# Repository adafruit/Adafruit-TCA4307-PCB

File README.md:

## Adafruit TCA4307 Hot-Swap I2C Buffer with Stuck Bus Recovery PCB

<a href="http://www.adafruit.com/products/5159"><br/>
Click here to purchase one from the Adafruit shop</a>

PCB files for the Adafruit TCA4307 Hot-Swap I2C Buffer with Stuck Bus Recovery. 

Format is EagleCAD schematic and board layout
* https://www.adafruit.com/product/5159

### Description

As we've been adding  STEMMA QT connectors to our breakouts and dev boards, folks have been really enjoying the simplicity and speed of plugging in I2C sensors and devices for quick iteration and design. That's all good, but I2C wasn't really designed for hot-plugging. You're kinda supposed to have everything connected once on boot and never mess with it - I2C was specified for on-board connections. And, folks who have experimented with hot-plugging I2C devices eventually have discovered that if you plug in or unplug at the wrong moment you can cause the bus to hang due to an extra SCL pulse or an unexpected capacitive load.

The Adafruit TCA4307 Hot-Swap I2C Buffer breakout here solves that problem. It's specifically designed to take a non-hot-swap protocol (I2C) and protect the controller from wayward peripherals messing with the bus during attach/detach.

Usage is super simple. Connect the left side (IN) to your main board controller - Arduino, Raspberry Pi, Feather, etc. Then connect any I2C sensors you like to OUT side. Power is connected through - this isn't a power isolator, just a bus buffer. You can use 2.3 to 5.5V DC power and logic levels.

The chip can handle up to 400KHz I2C clock rates and even has stuck bus recovery: it automatically disconnects the bus if it detects either SDAOUT or SCLOUT are low for about 40 ms. Once the bus is disconnected, the device automatically generates up to 16 pulses on SCLOUT to attempt to reset the device which is holding the bus low.

There's also an extra ENable pin, if you want to disconnect the in and out sides, and a READY pin that will let you know if the peripheral is buffer-connected to the controller (and is safe to attempt communication with)

To get you going fast, we spun up a custom-made PCB in the STEMMA QT form factor, making it easy to interface with. The STEMMA QT connectors on either side are compatible with the SparkFun Qwiic I2C connectors. This allows you to make solderless connections between your development board and the TCA4307 or to chain it with a wide range of other sensors and accessories using a compatible cable. QT Cable is not included, but we have a variety in the shop.

### License

Adafruit invests time and resources providing this open source design, please support Adafruit and open-source hardware by purchasing products from [Adafruit](https://www.adafruit.com)!

Designed by Limor Fried/Ladyada for Adafruit Industries.

Creative Commons Attribution/Share-Alike, all text above must be included in any redistribution. 
See license.txt for additional details.

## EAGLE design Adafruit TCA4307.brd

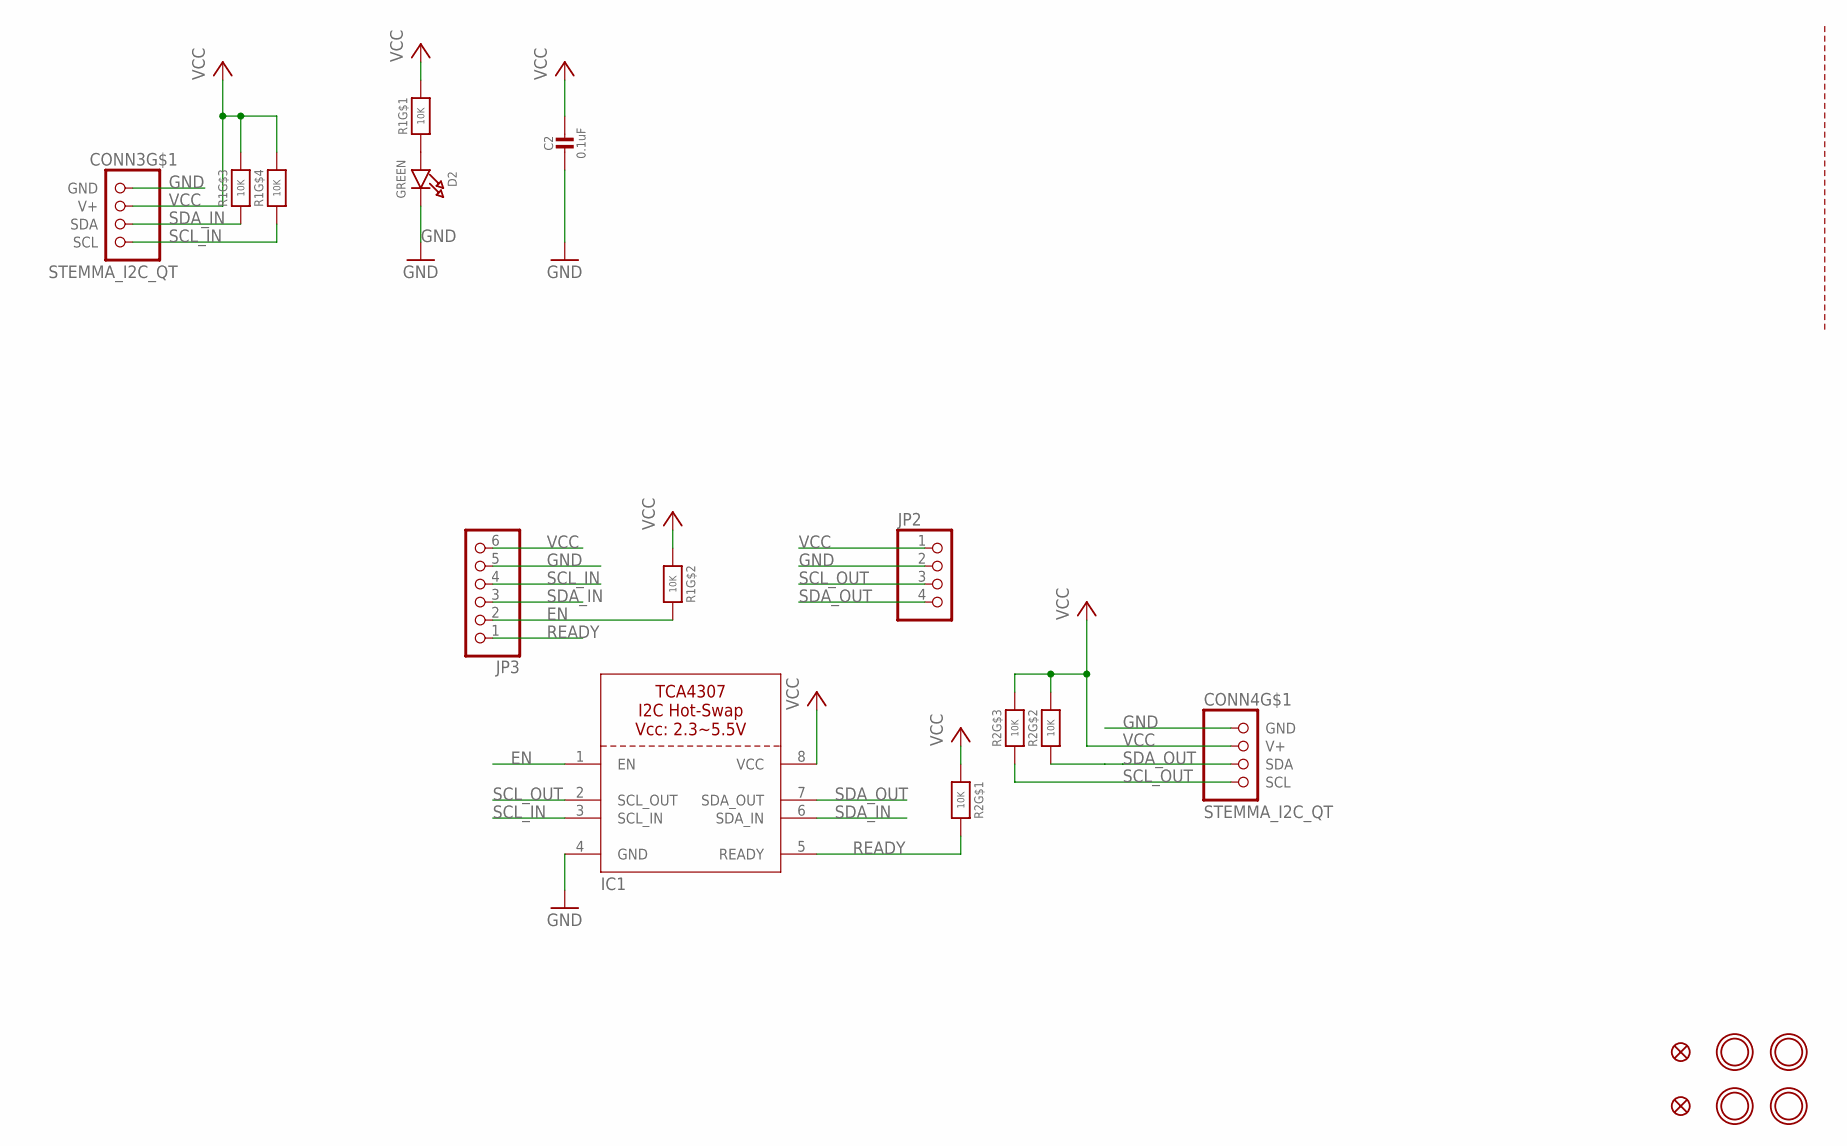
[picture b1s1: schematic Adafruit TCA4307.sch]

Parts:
C2: 0.1uF; 0603-NO
CONN3, CONN4: STEMMA_I2C_QT; JST_SH4
D2: GREEN; CHIPLED_0603_NOOUTLINE
FID3, FID4: FIDUCIAL_1MM
IC1: TCA4307; TSSOP8
JP2: HEADER-1X4ROUND; 1X04_ROUND
JP3: HEADER-1X670MIL; 1X06_ROUND_70
R1, R2: 10K; RESPACK_4X0603
U$1, U$17, U$19, U$21: MOUNTINGHOLE2.5; MOUNTINGHOLE_2.5_PLATED

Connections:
EN: IC1.1 (EN), JP3.2, R1.7 (2)
GND: C2.2, CONN3.1 (GND), CONN4.1 (GND), D2.C, IC1.4 (GND), JP2.2, JP3.5
unnamed: D2.A, R1.1
READY: IC1.5 (READY), JP3.1, R2.8 (2)
SCL_IN: CONN3.4 (SCL), IC1.3 (SCL_IN), JP3.4, R1.4 (1)
SCL_OUT: CONN4.4 (SCL), IC1.2 (SCL_OUT), JP2.3, R2.3 (1)
SDA_IN: CONN3.3 (SDA), IC1.6 (SDA_IN), JP3.3, R1.3 (1)
SDA_OUT: CONN4.3 (SDA), IC1.7 (SDA_OUT), JP2.4, R2.2 (1)
VCC: C2.1, CONN3.2 (V+), CONN4.2 (V+), IC1.8 (VCC), JP2.1, JP3.6, R1.2 (1), R1.5 (2), R1.6 (2), R1.8 (2), R2.1, R2.6 (2), R2.7 (2)

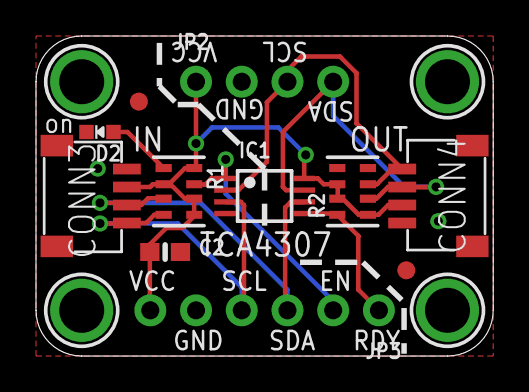
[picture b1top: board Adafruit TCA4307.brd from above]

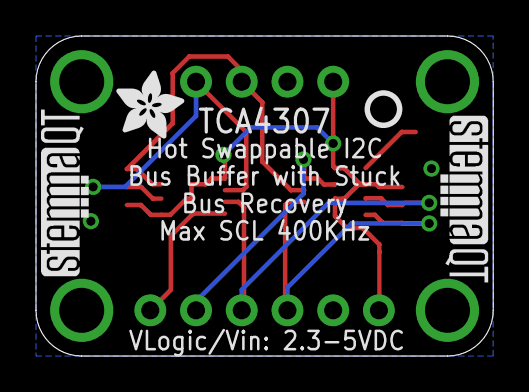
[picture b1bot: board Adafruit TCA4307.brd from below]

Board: 2 copper layers, 25.4 x 17.8 mm, 19 parts (4 on the bottom side), 9 nets.

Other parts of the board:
U$2: ADAFRUIT_3.5MM
U$25: PCBFEAT-REV-040
U$30, U$31: STEMMAQT

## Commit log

2021-07-15 Adding board files.

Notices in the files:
parts and their libraries:
microbuilder: This work is placed in the public domain, and may be freely used for commercial and non-commercial work with the following conditions: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
